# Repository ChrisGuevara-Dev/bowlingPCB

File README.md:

# Bowling PCB
This project focused on creating a printed circuit board (PCB) for the precise control of a bowling machine, utilizing the KiCAD design platform and the ESP32 microcontroller. The compact and robust design aimed to enhance the accuracy and reliability of ball launches, providing a comprehensive solution compatible with KiCAD standards.

## Schematic

## 3D Model & Footprint

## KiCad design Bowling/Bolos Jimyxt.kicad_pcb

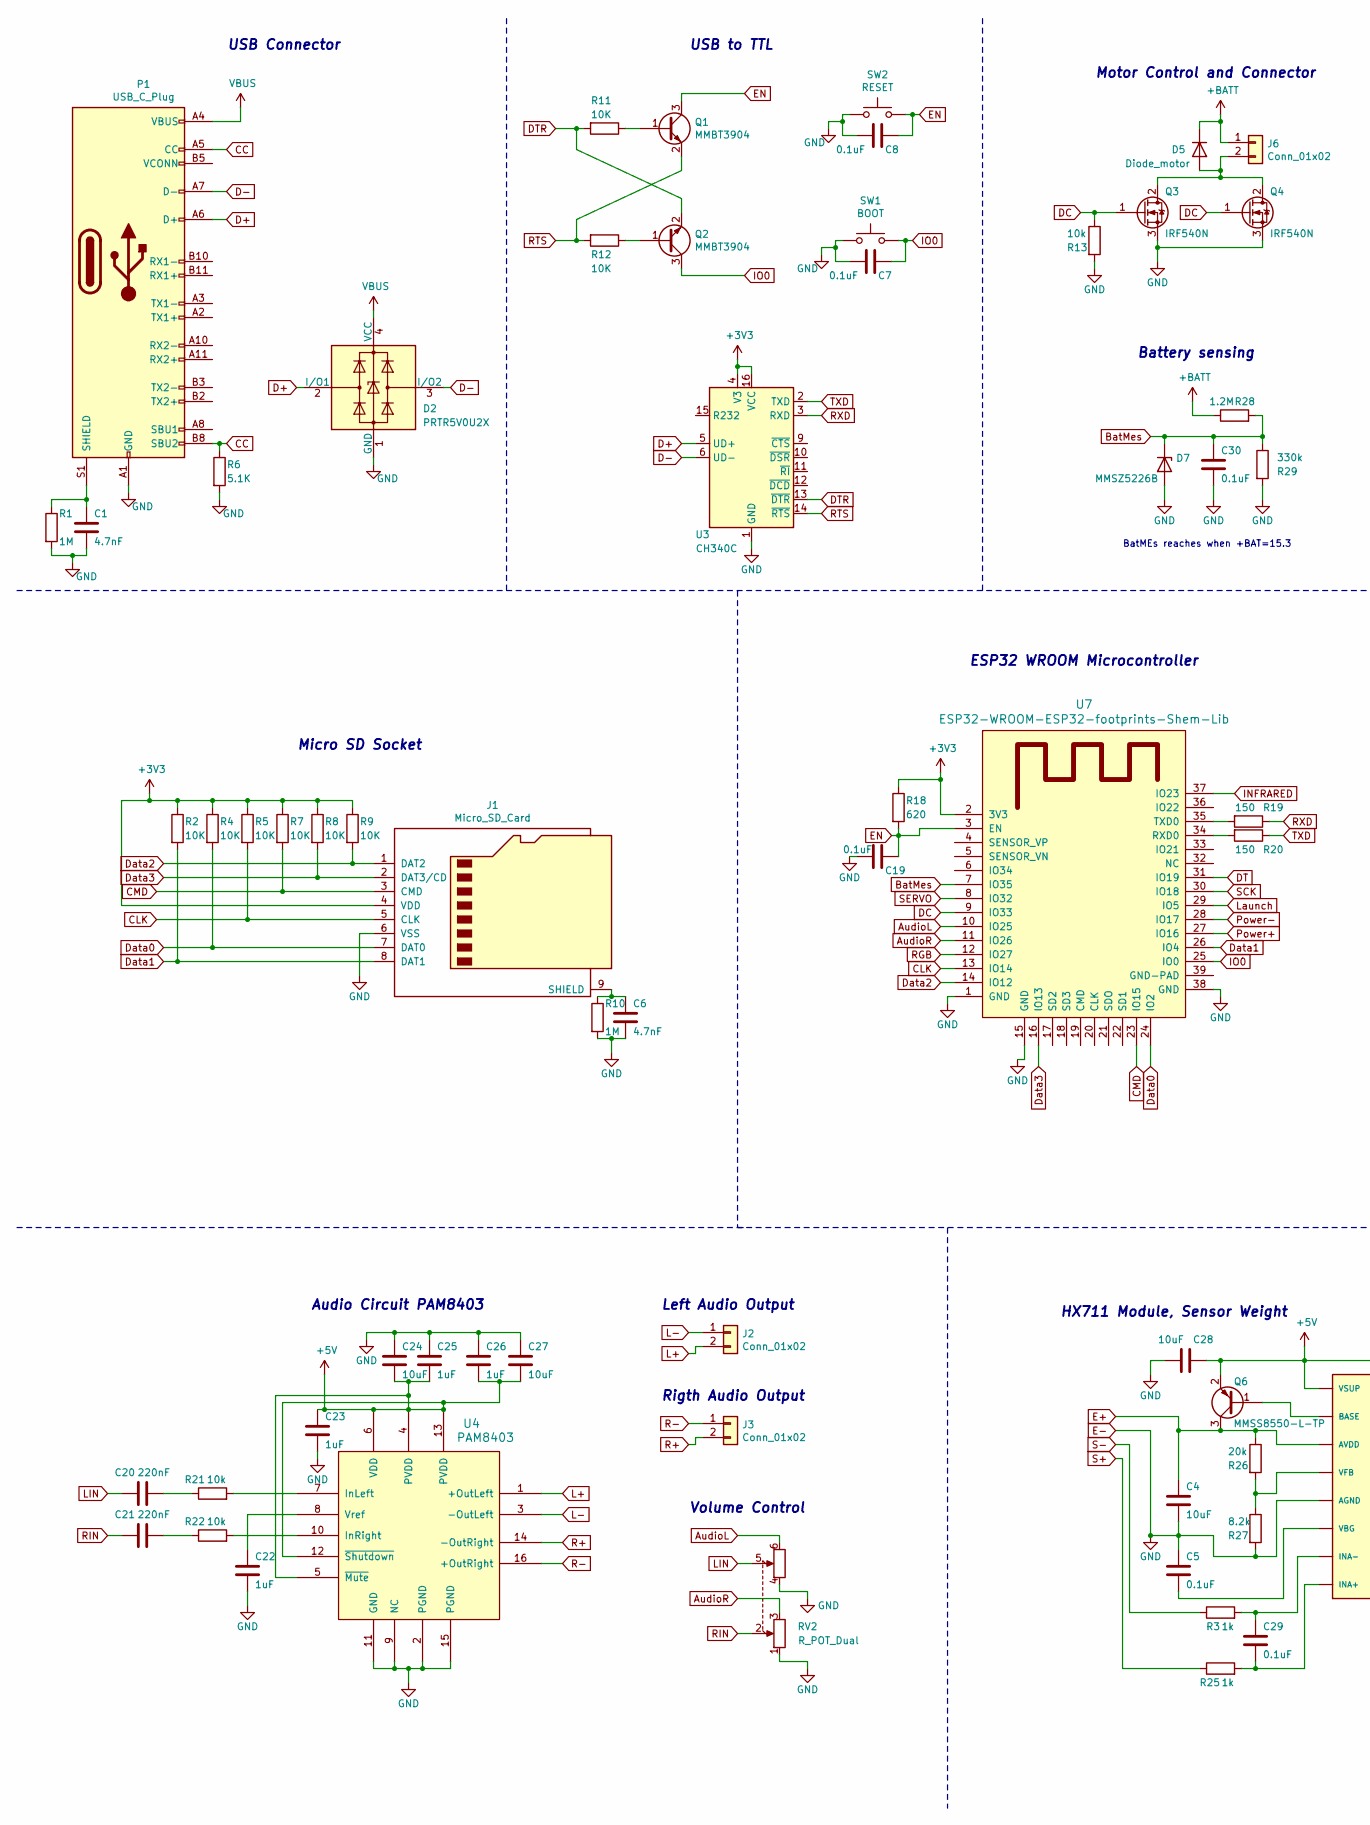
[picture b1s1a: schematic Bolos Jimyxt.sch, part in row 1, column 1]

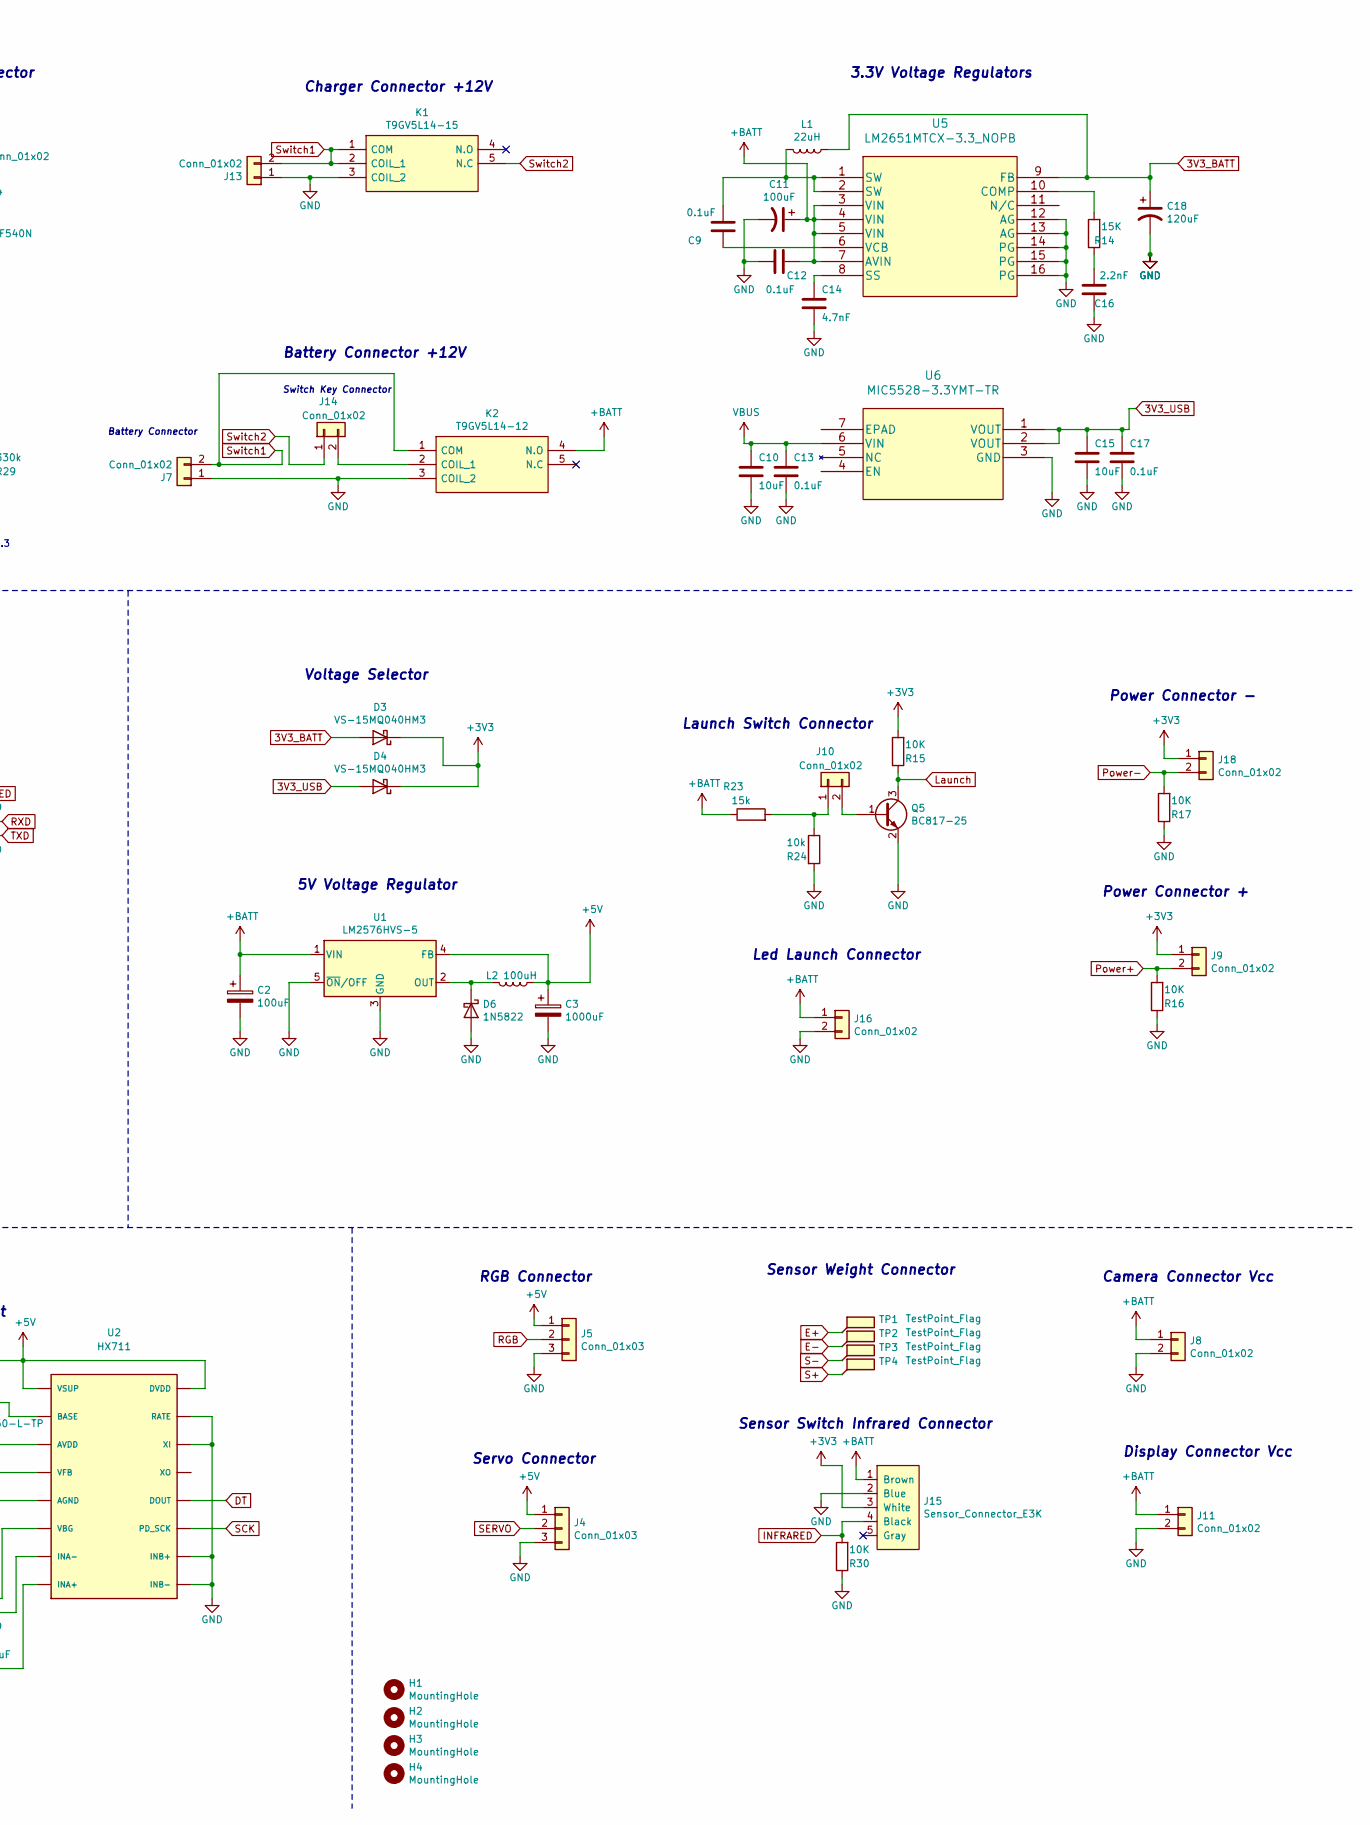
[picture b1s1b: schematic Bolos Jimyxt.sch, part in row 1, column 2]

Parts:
C1, C6, C14: 4.7nF; C_0805_2012Metric; MFG PN C0805C472J3GEC7210
C2, C11: 100uF; CP_Elec_5x5.8; MFG PN EEE-FK1C101SR
C3: 1000uF; UUG1A102MNQ1MS; MFG PN UUG1A102MNQ1MS
C4, C10, C15, C24, C27, C28: 10uF; C_0805_2012Metric; MFG PN C2012X5R1E106M125AB
C5, C7, C8, C9, C12, C13, C17, C19, C29, C30: 0.1uF; C_0805_2012Metric; MFG PN C0805C104J3RECAUTO7210
C16: 2.2nF; C_0805_2012Metric; MFG PN C0805C222K3GECTU
C18: 120uF; CP_Elec_5x5.8; MFG PN EEE-FK1A121SR
C20, C21: 220nF; C_0805_2012Metric; MFG PN C0805C224J3RACTU
C22, C23, C25, C26: 1uF; C_0805_2012Metric; MFG PN C0805C105M3REC7210
D2: PRTR5V0U2X; SOT-143; MFG PN PRTR5V0U2X,215
D3, D4: VS-15MQ040HM3; VS-15MQ040NPBF; MFG PN VS-15MQ040HM3/5AT
D5: Diode_motor; TO-263-2; MFG PN PSDB3060S1_T0_00001
D6: 1N5822; SS3040HE_R1_00001; MFG PN SS3040HE_R1_00001
D7: MMSZ5226B; D_SOD-123; MFG PN MMSZ5226B_R1_00001
H1, H2, H3, H4: MountingHole; MountingHole_3.2mm_M3; MFG PN DNP
J1: Micro_SD_Card; microSD_HC_Molex_104031-0811; MFG PN 104031-0811
J2, J3, J8, J9, J10, J11, J14, J16, J18: Conn_01x02; 397730002; MFG PN 39773-0002
J4, J5: Conn_01x03; JST_XH_S3B-XH-A_1x03_P2.50mm_Horizontal; MFG PN S3B-XH-A(LF)(SN)
J6, J7: Conn_01x02; TB00576202BE; MFG PN TB005-762-02BE
J13: Conn_01x02; BarrelJack_CUI_PJ-063AH_Horizontal; MFG PN PJ-063AH
J15: Sensor_Connector_E3K; 171856-0105; MFG PN 171856-0105
K1: T9GV5L14-15; T9GV5L145; Manufacturer_Part_Number T9GV5L14-5; Mouser Part Number 655-T9GV5L14-5
K2: T9GV5L14-12; T9GV5L145; Manufacturer_Part_Number T9GV5L14-5; Mouser Part Number 655-T9GV5L14-5
L1: 22uH; L_Sumida_CDMC6D28_7.25x6.5mm; MFG PN ASPI-0630LR-220M-T15
L2: 100uH; L_Vishay_IHLP-6767; MFG PN IHLP6767GZER101M11
P1: USB_C_Plug; USB_C_Receptacle_Amphenol_12401610E4-2A; MFG PN 12401610E4#2A
Q1, Q2: MMBT3904; SOT-323_SC-70; MFG PN MMBT3904W_R1_00001
Q3, Q4: IRF540N; TO-263-2; MFG PN IRF540SPBF
Q5: BC817-25; SOT-323_SC-70; MFG PN BC817-25_R1_00001
Q6: MMSS8550-L-TP; SOT-23; MFG PN MMSS8550-L-TP
R1, R10: 1M; R_0805_2012Metric; MFG PN CMP0805-FX-1004ELF
R2, R4, R5, R7, R8, R9, R11, R12, R15, R16, R17, R30: 10K; R_0805_2012Metric; MFG PN ERJ-UP6J103V
R3, R25: 1k; R_0805_2012Metric; MFG PN ERJ-P06F1001V
R6: 5.1K; R_0805_2012Metric; MFG PN ERJ-T06J512V
R13, R21, R22, R24: 10k; R_0805_2012Metric; MFG PN ERJ-UP6J103V
R14: 15K; R_0805_2012Metric; MFG PN ERJ-P06F1502V
R18: 620; R_0805_2012Metric; MFG PN ERJ-P06J621V
R19, R20: 150; R_0805_2012Metric; MFG PN ERJ-P06F1500V
R23: 15k; R_0805_2012Metric; MFG PN ERJ-P06F1502V
R26: 20k; R_0805_2012Metric; MFG PN ERJ-P06J203V
R27: 8.2k; R_0805_2012Metric; MFG PN ERJ-P06F8201V
R28: 1.2M; R_0805_2012Metric; MFG PN ERJ-P06J125V
R29: 330k; R_0805_2012Metric; MFG PN ERJ-T06J334V
RV2: R_POT_Dual; Potentiometer_Alps_RK163_Dual_Horizontal; MFG PN RK16312A0BKH
SW1: BOOT; LL3301FF065QJ; MFG PN LL3301AF065QJ
SW2: RESET; LL3301FF065QJ; MFG PN LL3301AF065QJ
TP1, TP2, TP3, TP4: TestPoint_Flag; TestPoint_Pad_D1.5mm; MFG PN DNP
U1: LM2576HVS-5; TO-263-5_TabPin3; MFG PN LM2576HVS-5.0/NOPB
U2: HX711; SOP-16_3.9x9.9mm_P1.27mm; MFG PN HX711
U3: CH340C; SOIC-16_3.9x9.9mm_P1.27mm; MFG PN CH340C
U4: PAM8403; SOIC-16_3.9x9.9mm_P1.27mm; MFG PN PAM8403DR-H
U5: LM2651MTCX-3.3_NOPB; TSSOP-16_4.4x5mm_P0.65mm; MFG PN LM2651MTCX-3.3/NOPB
U6: MIC5528-3.3YMT-TR; MFG PN MIC5528-3.3YMT-TR
U7: ESP32-WROOM-ESP32-footprints-Shem-Lib; ESP32-WROOM-32 8MB; MFG PN ESP32-WROOM-32

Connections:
3V3_BATT: C18.1, D3.2 (A), L1.1, U5.9 (FB)
3V3_USB: C15.1, C17.1, D4.2 (A), U6.1 (VOUT), U6.2 (VOUT)
+3V3: D3.1 (K), D4.1 (K), J1.4 (VDD), J9.1, J15.3 (White), J18.1, R2.1, R4.1, R5.1, R7.1, R8.1, R9.1, R15.2, R18.1, U3.4 (V3), U3.16 (VCC), U7.2 (3V3)
+5V: C3.1, C23.1, C24.2, C25.2, C26.2, C27.2, C28.1, J4.1, J5.1, L2.1, Q6.2 (E), U1.4 (FB), U2.1 (VSUP), U2.16 (DVDD), U4.4 (PVDD), U4.5 (~Mute), U4.6 (VDD), U4.12 (~Shutdown), U4.13 (PVDD)
+BATT: C2.1, C11.1, C12.1, D5.1 (K), J6.1, J8.1, J11.1, J15.1 (Brown), J16.1, K2.4 (N.O), R23.1, R28.1, U1.1 (VIN), U5.3 (VIN), U5.4 (VIN), U5.5 (VIN), U5.7 (AVIN)
AudioL: RV2.6, U7.10 (IO25)
AudioR: RV2.3, U7.11 (IO26)
BatMes: C30.1, D7.1 (K), R28.2, R29.1, U7.7 (IO35)
CC: P1.A5 (CC), P1.B8 (SBU2), R6.1
CLK: J1.5 (CLK), R5.2, U7.13 (IO14)
CMD: J1.3 (CMD), R7.2, U7.23 (IO15)
D+: D2.2 (I/O1), P1.A6 (D+), U3.5 (UD+)
D-: D2.3 (I/O2), P1.A7 (D-), U3.6 (UD-)
DC: Q3.1 (G), Q4.1 (G), R13.1, U7.9 (IO33)
DT: U2.12 (DOUT), U7.31 (IO19)
DTR: Q2.2 (E), R11.2, U3.13 (~DTR)
Data0: J1.7 (DAT0), R4.2, U7.24 (IO2)
Data1: J1.8 (DAT1), R2.2, U7.26 (IO4)
Data2: J1.1 (DAT2), R9.2, U7.14 (IO12)
Data3: J1.2 (DAT3/CD), R8.2, U7.16 (IO13)
E+: C4.1, Q6.3 (C), R26.1, TP1.1, U2.3 (AVDD)
E-: C1.2, C2.2, C3.2, C4.2, C5.1, C6.2, C7.2, C8.2, C10.2, C11.2, C12.2, C13.2, C14.2, C15.2, C16.1, C17.2, C18.2, C19.2, C22.2, C23.2, C24.1, C25.1, C26.1, C27.1, C28.2, C30.2, D2.1 (GND), D6.2 (A), D7.2 (A), J1.6 (VSS), J4.3, J5.3, J7.1, J8.2, J11.2, J13.1, J15.2 (Blue), J16.2, K1.3 (COIL_2), K2.3 (COIL_2), P1.A1 (GND), P1.A12 (GND), P1.B1 (GND), P1.B12 (GND), Q3.3 (S), Q4.3 (S), Q5.2 (E), R1.2, R6.2, R10.2, R13.2, R16.1, R17.1, R24.2, R27.2, R29.2, R30.1, RV2.1, RV2.4, SW1.1, SW2.1, TP2.1, U1.3 (GND), U1.5 (~ON~/OFF), U2.5 (AGND), U2.9 (INB-), U2.10 (INB+), U2.14 (XI), U2.15 (RATE), U3.1 (GND), U4.2 (PGND), U4.9 (NC), U4.11 (GND), U4.15 (PGND), U5.12 (AG), U5.13 (AG), U5.14 (PG), U5.15 (PG), U5.16 (PG), U6.3 (GND), U7.1 (GND), U7.15 (GND), U7.38 (GND)
EN: C8.1, C19.1, Q1.3 (C), R18.2, SW2.2, U7.3 (EN)
INFRARED: J15.4 (Black), R30.2, U7.37 (IO23)
IO0: C7.1, Q2.3 (C), SW1.2, U7.25 (IO0)
L+: J2.2, U4.1 (+OutLeft)
L-: J2.1, U4.3 (-OutLeft)
LIN: C20.1, RV2.5
Launch: Q5.3 (C), R15.1, U7.29 (IO5)
unnamed: C1.1, P1.S1 (SHIELD), R1.1
unnamed: C5.2, U2.6 (VBG)
unnamed: C6.1, J1.9 (SHIELD), R10.1
unnamed: C9.1, U5.6 (VCB)
unnamed: C9.2, L1.2, U5.1 (SW), U5.2 (SW)
unnamed: C14.1, U5.8 (SS)
unnamed: C16.2, R14.1
unnamed: C20.2, R21.1
unnamed: C21.2, R22.1
unnamed: C22.1, U4.8 (Vref)
unnamed: C29.1, R3.2, U2.7 (INA-)
unnamed: C29.2, R25.2, U2.8 (INA+)
unnamed: D5.3 (A), J6.2, Q3.2 (D), Q4.2 (D)
unnamed: D6.1 (K), L2.2, U1.2 (OUT)
unnamed: J10.1, R23.2, R24.1
unnamed: J10.2, Q5.1 (B)
unnamed: J14.2, K2.2 (COIL_1)
unnamed: Q1.1 (B), R11.1
unnamed: Q2.1 (B), R12.1
unnamed: Q6.1 (B), U2.2 (BASE)
unnamed: R14.2, U5.10 (COMP)
unnamed: R19.2, U7.35 (TXD0)
unnamed: R20.2, U7.34 (RXD0)
unnamed: R21.2, U4.7 (InLeft)
unnamed: R22.2, U4.10 (InRight)
unnamed: R26.2, R27.1, U2.4 (VFB)
Power+: J9.2, R16.2, U7.27 (IO16)
Power-: J18.2, R17.2, U7.28 (IO17)
R+: J3.2, U4.14 (-OutRight)
R-: J3.1, U4.16 (+OutRight)
RGB: J5.2, U7.12 (IO27)
RIN: C21.1, RV2.2
RTS: Q1.2 (E), R12.2, U3.14 (~RTS)
RXD: R19.1, U3.3 (RXD)
S+: R25.1, TP4.1
S-: R3.1, TP3.1
SCK: U2.11 (PD_SCK), U7.30 (IO18)
SERVO: J4.2, U7.8 (IO32)
Switch1: J7.2, J13.2, K1.1 (COM), K1.2 (COIL_1), K2.1 (COM)
Switch2: J14.1, K1.5 (N.C)
TXD: R20.1, U3.2 (TXD)
VBUS: C10.1, C13.1, D2.4 (VCC), P1.A4 (VBUS), P1.A9 (VBUS), P1.B4 (VBUS), P1.B9 (VBUS), U6.6 (VIN)

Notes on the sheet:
USB Connector
USB to TTL
Micro SD Socket
3.3V Voltage Regulators
Voltage Selector
Motor Control and Connector
Battery Connector +12V
Servo Connector
Rigth Audio Output
Left Audio Output
Audio Circuit PAM8403
Camera Connector Vcc
Display Connector Vcc
Sensor Weight Connector
5V Voltage Regulator
Volume Control
Charger Connector +12V
HX711 Module, Sensor Weight
Power Connector -
Led Launch Connector
Launch Switch Connector
Battery sensing
Switch Key Connector
Battery Connector
ESP32 WROOM Microcontroller
Sensor Switch Infrared Connector
Power Connector +
RGB Connector
BatMEs reaches when +BAT=15.3

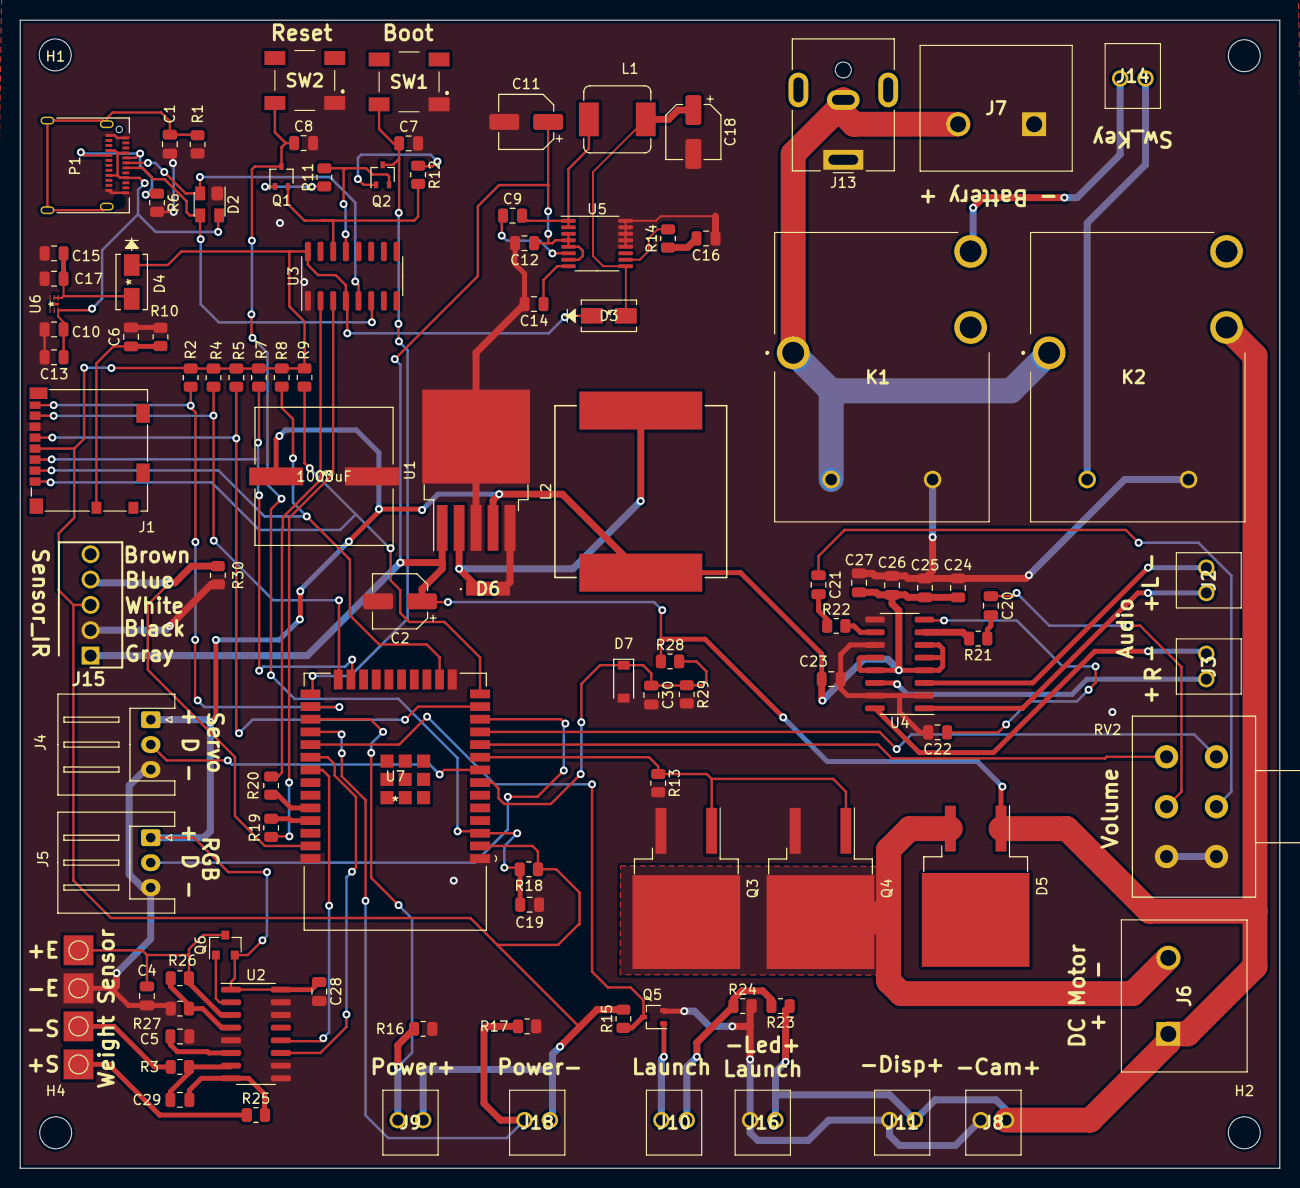
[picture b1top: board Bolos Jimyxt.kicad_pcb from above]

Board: 2 copper layers, 126.2 x 115.1 mm, 111 parts (0 on the bottom side), 71 nets.

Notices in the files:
parts and their libraries:
Copyright 2021 Accelerated Designs. All rights reserved.
